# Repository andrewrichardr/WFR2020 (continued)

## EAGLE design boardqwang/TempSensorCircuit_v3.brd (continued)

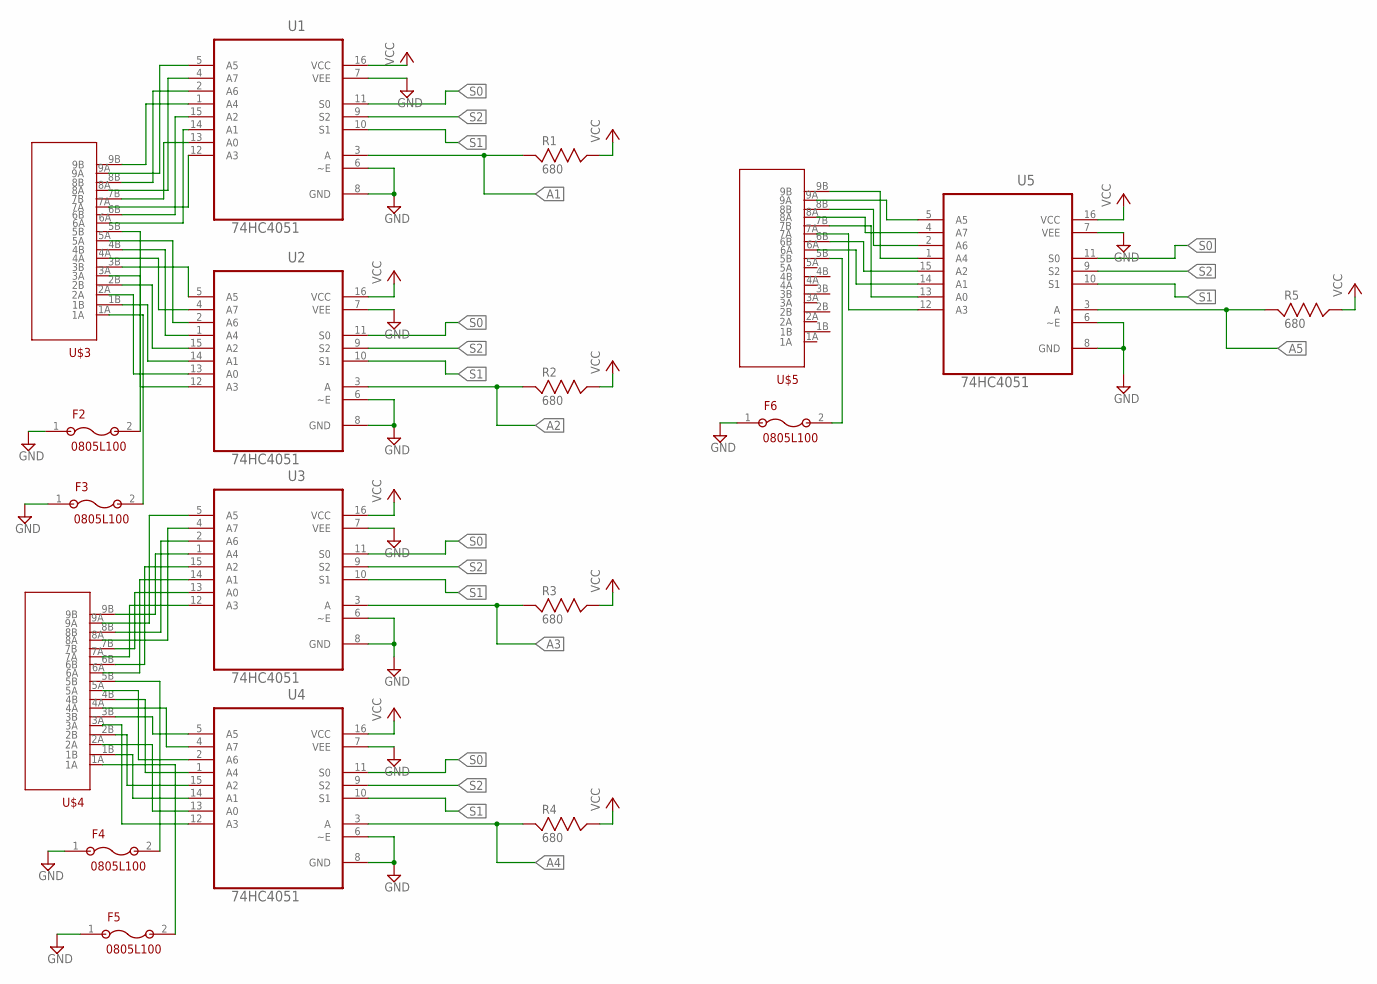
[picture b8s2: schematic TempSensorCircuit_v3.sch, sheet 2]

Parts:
F2, F3, F4, F5, F6: 0805L100; 2012
R1, R2, R3, R4, R5: 680; RESC2012X60
U1, U2, U3, U4, U5: 74HC4051; DIP254P762X508-16
U$3, U$4, U$5: WM1359-ND

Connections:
A1: R1.1, U1.3 (A); also elsewhere on the board
A2: R2.1, U2.3 (A); also elsewhere on the board
A3: R3.1, U3.3 (A); also elsewhere on the board
A4: R4.1, U4.3 (A); also elsewhere on the board
A5: R5.1, U5.3 (A); also elsewhere on the board
GND: F2.1, F3.1, F4.1, F5.1, F6.1, U1.6 (~E), U1.7 (VEE), U1.8 (GND), U2.6 (~E), U2.7 (VEE), U2.8 (GND), U3.6 (~E), U3.7 (VEE), U3.8 (GND), U4.6 (~E), U4.7 (VEE), U4.8 (GND), U5.6 (~E), U5.7 (VEE), U5.8 (GND); also elsewhere on the board
unnamed: U1.1 (A4), U$3.9B
unnamed: U1.2 (A6), U$3.8B
unnamed: U1.5 (A5), U$3.9A
unnamed: U1.4 (A7), U$3.8A
unnamed: U1.15 (A2), U$3.6B
unnamed: U1.14 (A1), U$3.6A
unnamed: U1.13 (A0), U$3.7B
unnamed: U1.12 (A3), U$3.7A
unnamed: U2.2 (A6), U$3.5A
unnamed: U2.1 (A4), U$3.4B
unnamed: U2.4 (A7), U$3.4A
unnamed: U2.5 (A5), U$3.3B
unnamed: U2.15 (A2), U$3.2B
unnamed: U2.14 (A1), U$3.1B
unnamed: U2.12 (A3), U$3.3A
unnamed: U2.13 (A0), U$3.2A
unnamed: F2.2, U$3.5B
unnamed: F3.2, U$3.1A
unnamed: U3.1 (A4), U$4.9B
unnamed: U3.2 (A6), U$4.8B
unnamed: U3.4 (A7), U$4.8A
unnamed: U3.5 (A5), U$4.9A
unnamed: U3.15 (A2), U$4.6B
unnamed: U3.14 (A1), U$4.6A
unnamed: U3.13 (A0), U$4.7B
unnamed: U3.12 (A3), U$4.7A
unnamed: F4.2, U$4.5B
unnamed: U4.1 (A4), U$4.4B
unnamed: U4.2 (A6), U$4.5A
unnamed: U4.4 (A7), U$4.4A
unnamed: U4.5 (A5), U$4.3B
unnamed: U4.15 (A2), U$4.2B
unnamed: U4.14 (A1), U$4.1B
unnamed: U4.13 (A0), U$4.2A
unnamed: U4.12 (A3), U$4.3A
unnamed: F5.2, U$4.1A
unnamed: U5.1 (A4), U$5.9B
unnamed: U5.2 (A6), U$5.8B
unnamed: U5.4 (A7), U$5.8A
unnamed: U5.5 (A5), U$5.9A
unnamed: U5.15 (A2), U$5.6B
unnamed: U5.14 (A1), U$5.6A
unnamed: U5.13 (A0), U$5.7B
unnamed: U5.12 (A3), U$5.7A
unnamed: F6.2, U$5.5B
S0: U1.11 (S0), U2.11 (S0), U3.11 (S0), U4.11 (S0), U5.11 (S0); also elsewhere on the board
S1: U1.10 (S1), U2.10 (S1), U3.10 (S1), U4.10 (S1), U5.10 (S1); also elsewhere on the board
S2: U1.9 (S2), U2.9 (S2), U3.9 (S2), U4.9 (S2), U5.9 (S2); also elsewhere on the board
VCC: R1.2, R2.2, R3.2, R4.2, R5.2, U1.16 (VCC), U2.16 (VCC), U3.16 (VCC), U4.16 (VCC), U5.16 (VCC); also elsewhere on the board

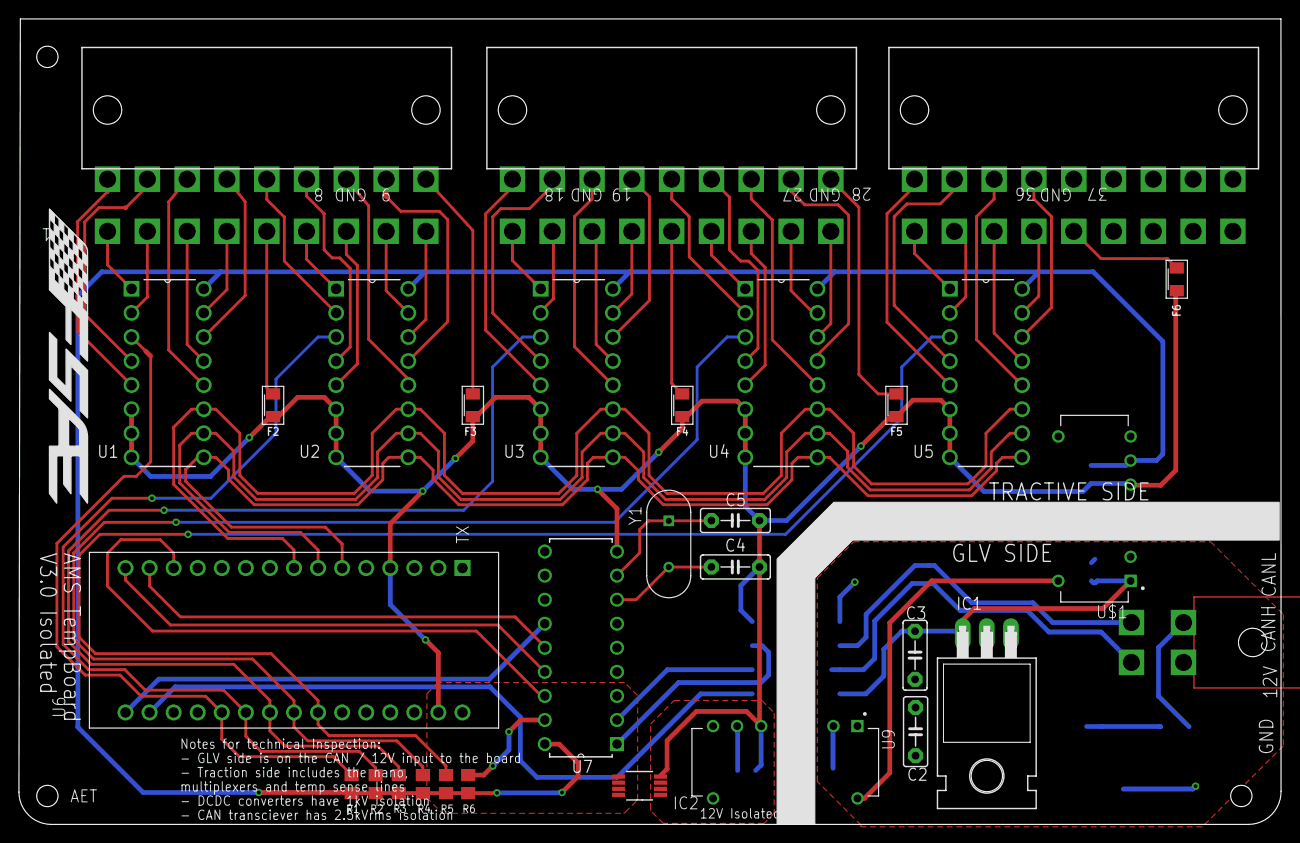
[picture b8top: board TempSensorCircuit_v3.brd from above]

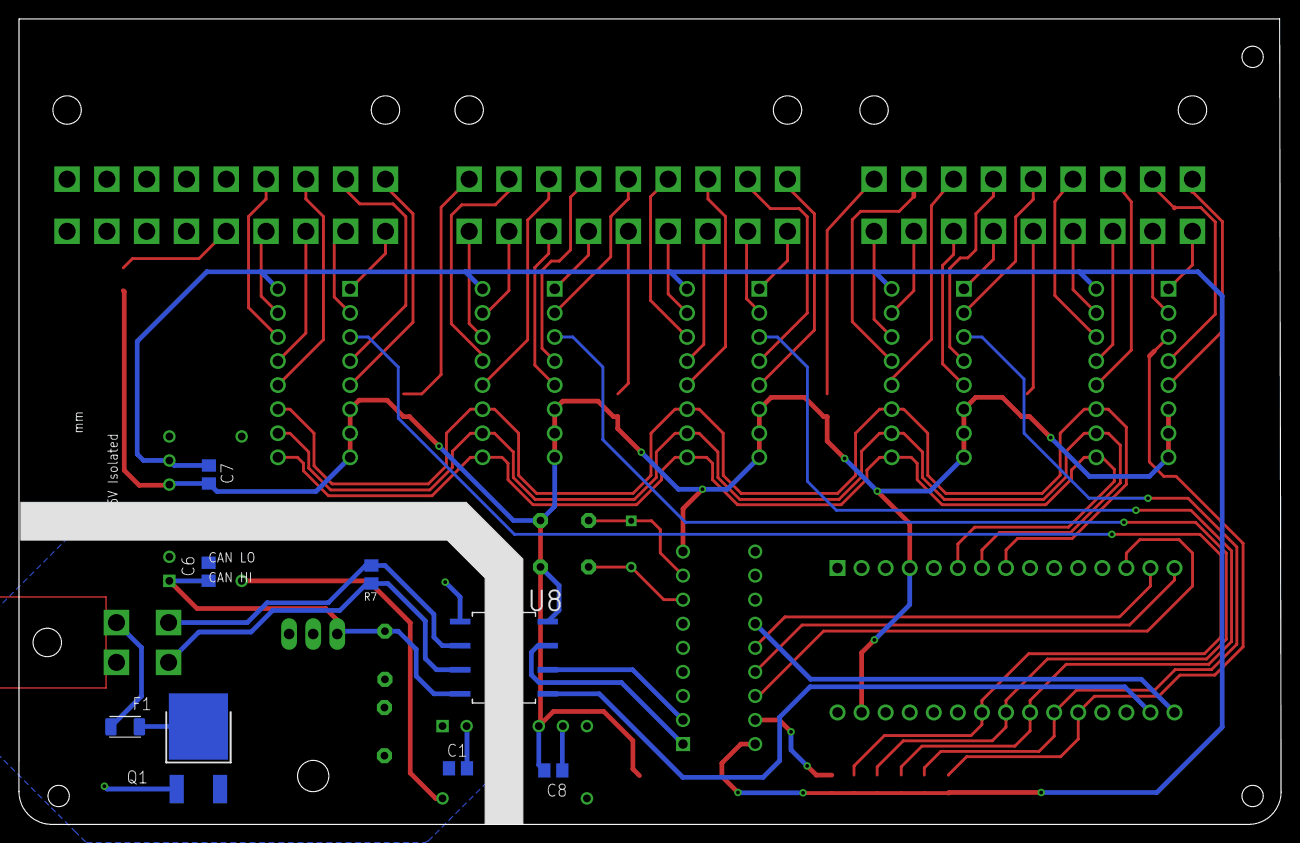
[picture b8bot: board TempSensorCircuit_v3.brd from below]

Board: 2 copper layers, 133.2 x 85.0 mm, 39 parts (8 on the bottom side), 74 nets.

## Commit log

2019-08-28 Mobo pathfinding
2019-09-05 mobo update
2019-09-20 push
2019-09-24 main
2019-10-01 model
2019-10-17 7792 added to all DC
2019-10-17 AIRDC - adjusted overall board length and nut position
2019-10-18 spelling
2019-12-10 stuff
2019-12-12 not an update
2020-07-07 Bump electron from 1.8.8 to 9.1.0 in /circuitjs1/resources/app
    Bumps [electron](https://github.com/electron/electron) from 1.8.8 to 9.1.0.
    - [Release notes](https://github.com/electron/electron/releases)
    - [Changelog](https://github.com/electron/electron/blob/master/docs/breaking-changes.md)
    - [Commits](https://github.com/electron/electron/compare/v1.8.8...v9.1.0)
